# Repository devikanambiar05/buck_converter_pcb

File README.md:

# 555-Based Low-Side Buck Converter

A step-down (buck) DC-DC converter that uses a **555 timer** for PWM and an **N-channel MOSFET on the low side**, so the 555 drives the gate directly. No gate driver or level shifter is needed. Designed in **KiCad 10** as a through-hole, two-layer board for a **12 V input and about 5 V output**.

This README also records how the design arrived at this circuit.

> **Status:** PCB designed. The 555 oscillator is verified on the bench. Power-stage testing is in progress (see [Results](#results)).

---

## Repository contents

| File | Description |
|---|---|
| `Buck_converter.kicad_sch` | Schematic |
| `Buck_converter.kicad_pcb` | PCB layout: 2-layer, 83.5 mm × 48 mm, through-hole |
| `Buck_converter.kicad_pro` | KiCad project file |

---

## Circuit overview

- **Timer:** NE555 in astable mode.
- **Duty-cycle control:** potentiometer with two steering diodes, so the duty cycle (and output voltage) is adjustable while the frequency stays almost constant.
- **Switch:** IRF740 N-MOSFET on the low side, driven from the 555 output through a 100 Ω gate resistor.
- **Power stage:** 220 µH inductor, 1N5822 Schottky diode, 220 µF output capacitor.
- **Terminals:** `J2` powers the 555 side, `J3` is the power-stage input, `J1` is the output. All share one ground, so a single 12 V supply can feed both inputs.

The output is **not ground-referenced**: `VOUT+` is the input `+` rail, and `VOUT−` floats above ground.

---

## Design journey

**1. Reference circuit.** The starting point was a 555 "buck converter" schematic with a potentiometer and a low-side MOSFET. It only generates PWM and switches the supply. It has no inductor, freewheel diode or output capacitor, so adding that L-D-C stage was the first change.

**2. Keeping it simple.** A 555 boost converter reference showed a simpler idea: the 555 drives a low-side N-MOSFET directly. A standard buck uses a high-side switch, which needs a gate driver or level shifter. That added too much complexity to both the circuit and the PCB, so I looked for a simpler arrangement.

**3. Low-side buck.** The switch can stay on the low side if the inductor and diode are mirrored: the switch connects the inductor to ground, the diode runs from the switch node to the positive rail, and the output capacitor sits between the positive rail and the inductor's far end. This negative-side buck still gives `Vout ≈ D × Vin`, and the 555 drives the gate directly. The trade-off is a floating output, which is acceptable for a self-contained load.

**4. PCB.** The board uses a potentiometer-controlled 555 for adjustable output, with separate input terminals for the 555 side and the power stage.

**5. Bench.** The resistor stock had no 1 kΩ or 10 kΩ values, so the oscillator was first built as a fixed astable with 680 Ω, 27 kΩ and 1.2 nF (plus 100 nF on pin 5). It gives a clean 50% square wave, ready to be connected to the power stage.

---

## PCB vs. bench oscillator

Both are astable 555 circuits driving the same power stage. The bench version is the simplest oscillator, used to prove the 555 side first. The PCB version adds a potentiometer and steering diodes for adjustable duty cycle, and around mid-travel it behaves like the fixed 50% version.

| | PCB (potentiometer) | Bench (fixed astable) |
|---|---|---|
| Timing network | `R2` 1 kΩ, `RV1`, `D2`/`D3`, `C2` 1 nF | 680 Ω, 27 kΩ, 1.2 nF |
| Pin 5 capacitor | 100 nF | 100 nF |
| Duty cycle | Adjustable | 50% |
| Frequency | about 28 kHz (calculated, 50 kΩ pot) | 17.45 kHz (measured) |

The power stage is identical in both, so bench results carry over to the PCB.

---

## Bill of materials

| Ref | Value | Footprint |
|---|---|---|
| U1 | NE555 | DIP-8 |
| Q2 | IRF740 | TO-220 vertical |
| D1 | 1N5822 (Schottky) | DO-201AD |
| D2, D3 | Small-signal diode (e.g. 1N4148) | DO-35 |
| L1 | 220 µH | Radial 12 mm (Fastron 11P) |
| C1 | 220 µF, polarized | Radial 8 mm |
| C2 | 1 nF | Disc 5 mm |
| C3 | 100 nF | Disc 5 mm |
| C4 | 100 µF, polarized | Radial 8 mm |
| R1 | 100 Ω (gate resistor) | Axial DIN0207 |
| R2 | 1 kΩ (pin 7 pull-up) | Axial DIN0207 |
| RV1 | Trimmer potentiometer (50 kΩ assumed) | Bourns 3296W vertical |
| J1, J2, J3 | Screw terminal, 5.08 mm | Phoenix MKDS 1,5/2-5.08 |

Capacitors should be rated 25 V or more. On polarized capacitors, pin 1 is positive.

---

## Netlist

| Net | Connections |
|---|---|
| **VIN+ / VOUT+** | J3-2, D1 cathode, C1 (+), J1-1 |
| **SW** (switch node) | Q2 drain, D1 anode, L1 pin 1 |
| **VOUT−** | L1 pin 2, C1 (−), J1-2 |
| **GND** | Q2 source, J2-1, J3-1, U1 pin 1, C2, C3, C4 (−) |
| **555 supply** | J2-2, U1 pins 4 and 8, R2 pin 1, C4 (+) |
| **Gate** | U1 pin 3 → R1 → Q2 gate |
| **Timing node** | U1 pins 2 and 6, RV1 wiper, C2 |
| **Pin 7 node** | U1 pin 7, R2 pin 2, D2 anode, D3 cathode |

---

## Results

| Test | Result |
|---|---|
| 555 astable oscillator (bench) | 17.45 kHz, 57.24 µs period, 50% duty, mean 5.5 V, RMS 7.82 V |
| Full buck stage at 12 V in | *to be added* |
| Efficiency | *to be added* |
| Output ripple | *to be added* |

---

## Lessons learned

- A PWM stage alone is not a buck converter. It needs the inductor, freewheel diode and output capacitor.
- The switch position sets the drive complexity. A low-side switch removes the need for a gate driver, at the cost of a floating output.
- Check the 555 mode in a diagram: a push-button trigger means monostable, which never gives a continuous square wave.
- Parts on hand can shape the design. Without 1 kΩ or 10 kΩ resistors, 680 Ω and 27 kΩ still gave a clean 50% oscillator.
- Measured frequency (17.45 kHz) differed from the calculated value (about 22 kHz). This is within component tolerance and fine for this converter.

---

## Limitations and next steps

- Open-loop: the output varies with load and input voltage and is set by hand.
- Needs a minimum load for stable output; light loads push the output up.
- `D1` should be a Schottky or fast-recovery diode, not a standard rectifier.
- Next: finish power-stage testing, add test points and a ground pour, and consider a feedback loop.

---

## Safety

- `VOUT−` sits several volts above ground. Do not connect a grounded scope clip or grounded load to `VOUT+` or `VOUT−`.
- Start with a current-limited supply and a resistive load.

---

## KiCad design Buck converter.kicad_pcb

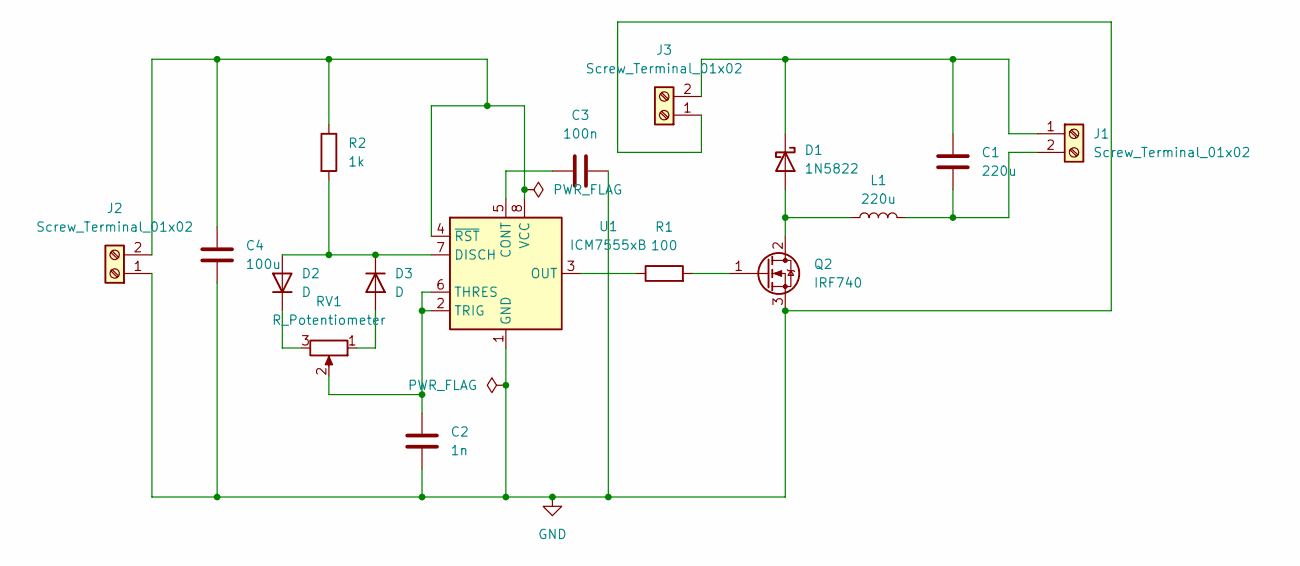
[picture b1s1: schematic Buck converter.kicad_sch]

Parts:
C1: 220u; CP_Radial_D8.0mm_P3.50mm
C2: 1n; C_Disc_D5.0mm_W2.5mm_P5.00mm
C3: 100n; C_Disc_D5.0mm_W2.5mm_P5.00mm
C4: 100u; CP_Radial_D8.0mm_P3.50mm
D1: 1N5822; D_DO-201AD_P15.24mm_Horizontal
D2, D3: D; D_DO-35_SOD27_P7.62mm_Horizontal
J1, J2, J3: Screw_Terminal_01x02; TerminalBlock_Phoenix_MKDS-1,5-2-5.08_1x02_P5.08mm_Horizont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
L1: 220u; L_Radial_D12.0mm_P5.00mm_Fastron_11P
Q2: IRF740; TO-220-3_Vertical
R1: 100; R_Axial_DIN0207_L6.3mm_D2.5mm_P7.62mm_Horizontal
R2: 1k; R_Axial_DIN0207_L6.3mm_D2.5mm_P7.62mm_Horizontal
RV1: R_Potentiometer; Potentiometer_Bourns_3296W_Vertical
U1: ICM7555xB; DIP-8_W7.62mm

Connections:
GND: C2.2, C3.2, C4.2, J2.1, J3.1, Q2.3 (S), U1.1 (GND)
unnamed: D1.2 (A), L1.1, Q2.2 (D)
unnamed: C1.1, D1.1 (K), J1.1, J3.2
unnamed: D2.2 (A), D3.1 (K), R2.2, U1.7 (DISCH)
unnamed: D2.1 (K), RV1.3
unnamed: D3.2 (A), RV1.1
unnamed: C1.2, J1.2, L1.2
unnamed: C4.1, J2.2, R2.1, U1.4 (~RST), U1.8 (VCC)
unnamed: Q2.1 (G), R1.2
unnamed: C3.1, U1.5 (CONT)
unnamed: R1.1, U1.3 (OUT)
unnamed: C2.1, RV1.2, U1.2 (TRIG), U1.6 (THRES)

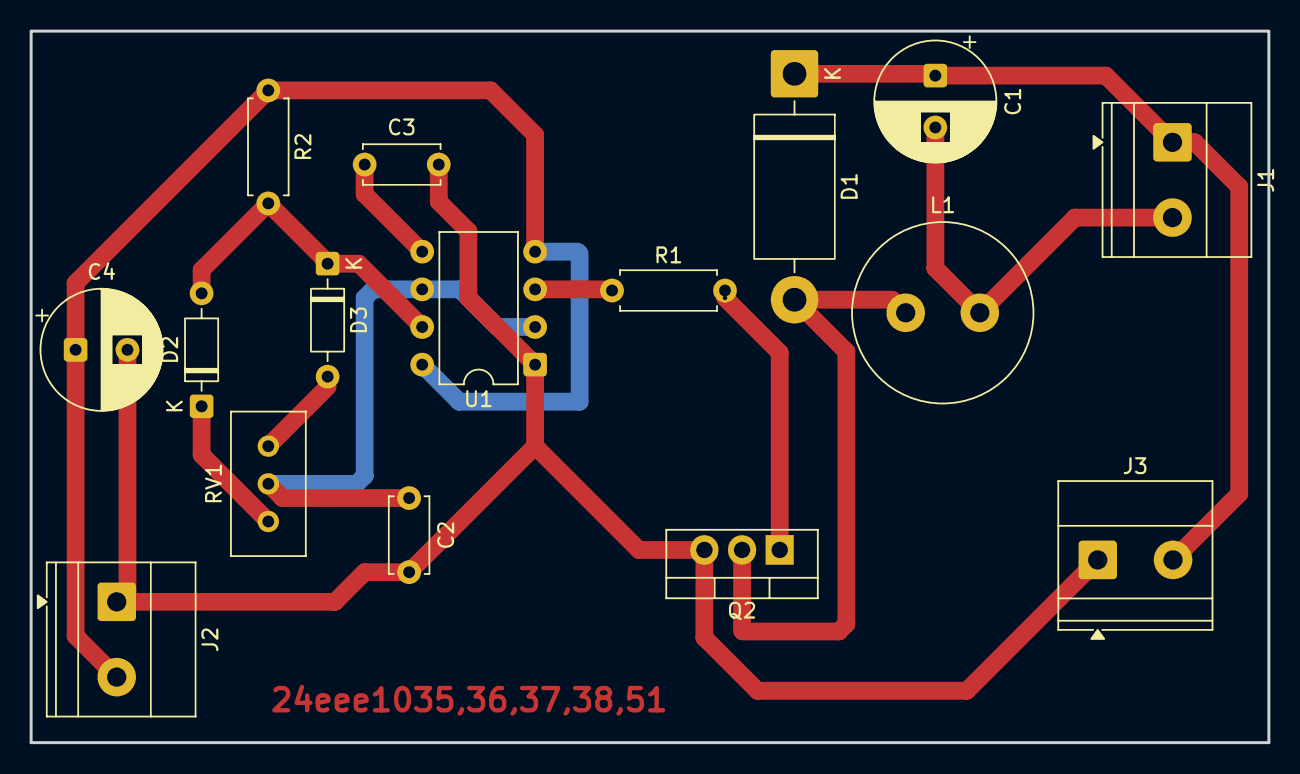
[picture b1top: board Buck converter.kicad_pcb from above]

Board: 2 copper layers, 83.5 x 48.0 mm, 16 parts (0 on the bottom side), 12 nets.
